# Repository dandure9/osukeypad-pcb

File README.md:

# osukeypad-pcb
 My very first keyboard PCB

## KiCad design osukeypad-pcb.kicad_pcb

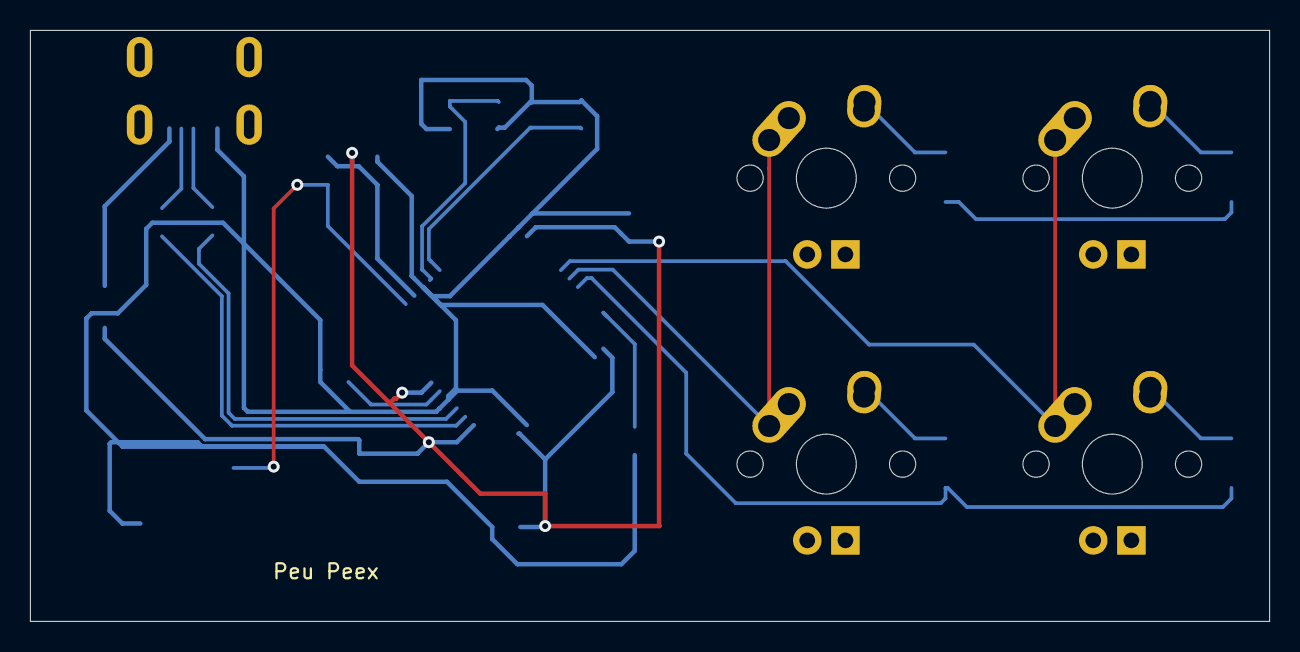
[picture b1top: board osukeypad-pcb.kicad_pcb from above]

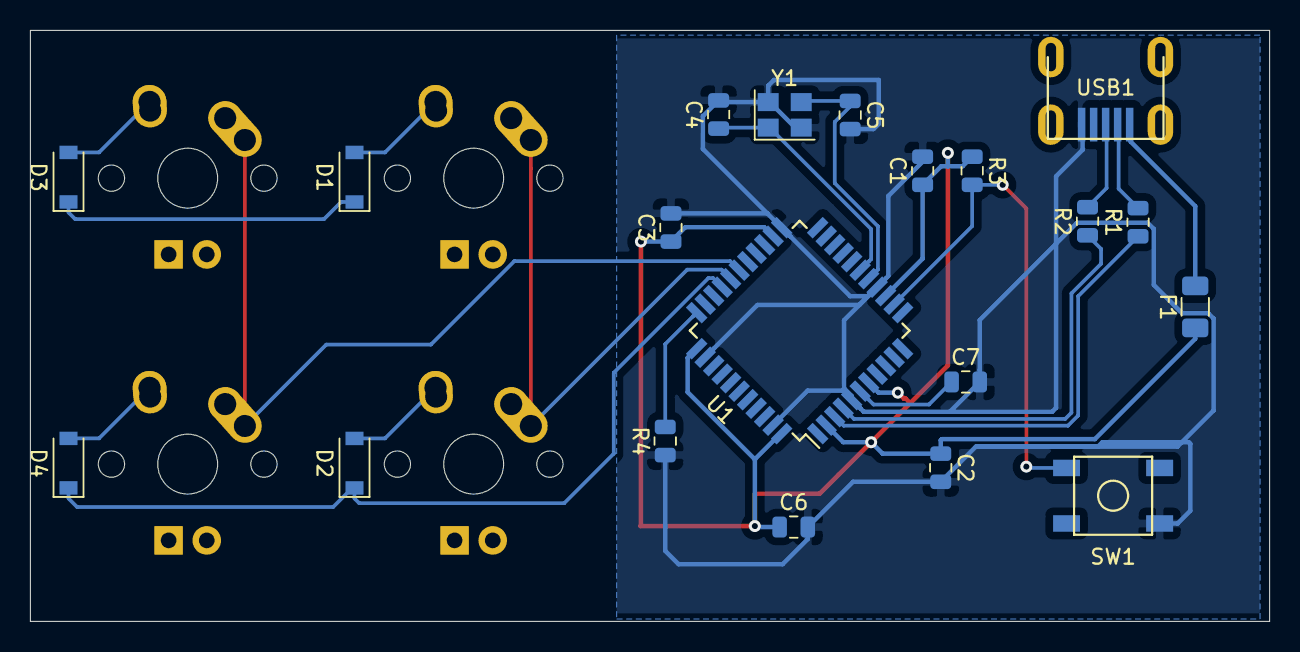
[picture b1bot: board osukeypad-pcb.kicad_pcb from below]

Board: 2 copper layers, 82.5 x 39.4 mm, 24 parts (20 on the bottom side), 20 nets.

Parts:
C1, C2, C3: 0.1uF; C_0805_2012Metric
C4, C5: 22pF; C_0805_2012Metric
C6: 10uF; C_0805_2012Metric
C7: 1uF; C_0805_2012Metric
D1, D2, D3, D4: SOD-123; D_SOD-123
F1: 500mA; Fuse_1206_3216Metric
MX1, MX2, MX3, MX4: MX-NoLED; MX-1U
R1, R2: 22ohm; R_0805_2012Metric
R3, R4: 10k; R_0805_2012Metric
SW1: SW_Push; SKQG-1155865
U1: ATmega32U4-AU; TQFP-44_10x10mm_P0.8mm
USB1: Molex-0548190589
Y1: 16MHz; Crystal_SMD_3225-4Pin_3.2x2.5mm

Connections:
+5V: C1.1, C2.1, C3.1, C6.1, F1.1, R3.1, U1.2, U1.7, U1.14, U1.24, U1.34, U1.44
COL0: MX1.1, MX2.1, U1.29
COL1: MX3.1, MX4.1, U1.28
D+: R2.2, USB1.3
D-: R1.2, USB1.4
GND: C1.2, C2.2, C3.2, C4.2, C5.2, C6.2, C7.2, R4.1, SW1.1, U1.5, U1.15, U1.23, U1.35, U1.43, USB1.1, Y1.2, Y1.4
unnamed: C4.1, U1.17, Y1.1
unnamed: C5.1, U1.16, Y1.3
unnamed: C7.1, U1.6
unnamed: D1.2, MX1.2
unnamed: D2.2, MX2.2
unnamed: D3.2, MX3.2
unnamed: D4.2, MX4.2
unnamed: R1.1, U1.3
unnamed: R2.1, U1.4
unnamed: R3.2, SW1.2, U1.13
unnamed: R4.2, U1.33
ROW0: D1.1, D3.1
ROW1: D2.1, D4.1, U1.30
VCC: F1.2, USB1.5

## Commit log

2022-12-31 Initialize project
2022-12-31 https://wiki.ai03.com/link/23#bkmrk-git-add-%2Agit-commit-
2022-12-31 Add footprint libraries
2023-01-01 osukeypad-update
2023-01-01 osukeypad-update-2
2023-01-01 osupad-update-3
2023-01-01 osukeypad-update-4
2023-01-01 osukeypad-update-5
2023-01-01 osukeypad-update-6
2023-01-02 osukeypad-update-7
2023-01-02 osukeypad-update-8
